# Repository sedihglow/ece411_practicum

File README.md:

# ece411_practicum
ece411 practicum project Team 16

# how to upload to ESP
1. Start upload from arduino IDE.
  - It will sit on connecting for this time.
2. Pull the reset pin low or unplug the device
3. Pull GPIO2 low with a button.
4. Let the reset pin go high or plug back in the device while gpio2 is low
  - The code should start uploading
5. let go of the GPIO2 button to ground.

# ESP setup program
1. Setup sensor pins
2. Setup I2C for moisture sensor
3. Try to connect to wifi using credentials in EEPROM
4. If credentials are bad, start a wifi hotspot on ESP
5. Connect to ESP using its wifi hotspot by connecting to the IP Address from a web browser
6. Once credentials are changed it reconnects using the new credentials.

# ESP main loop program flow
1. Check for user packet
2. if user sent a packet, handle the request for moisture threshold or pump time
3. read the moisture sensor
4. If the moisture sensor reads below threshold and water is in the tank, water plant
5. repeat 1-4

# user program
To compile use the makefile $make
To run you can use the makefile $make run
The user program will prompt the user with a menu
  - change moisture threshold
  - change pump time
  - exit program
  
The moisture threshold can be values of 1 to 1000

The pump time can be between 1 and 10 seconds

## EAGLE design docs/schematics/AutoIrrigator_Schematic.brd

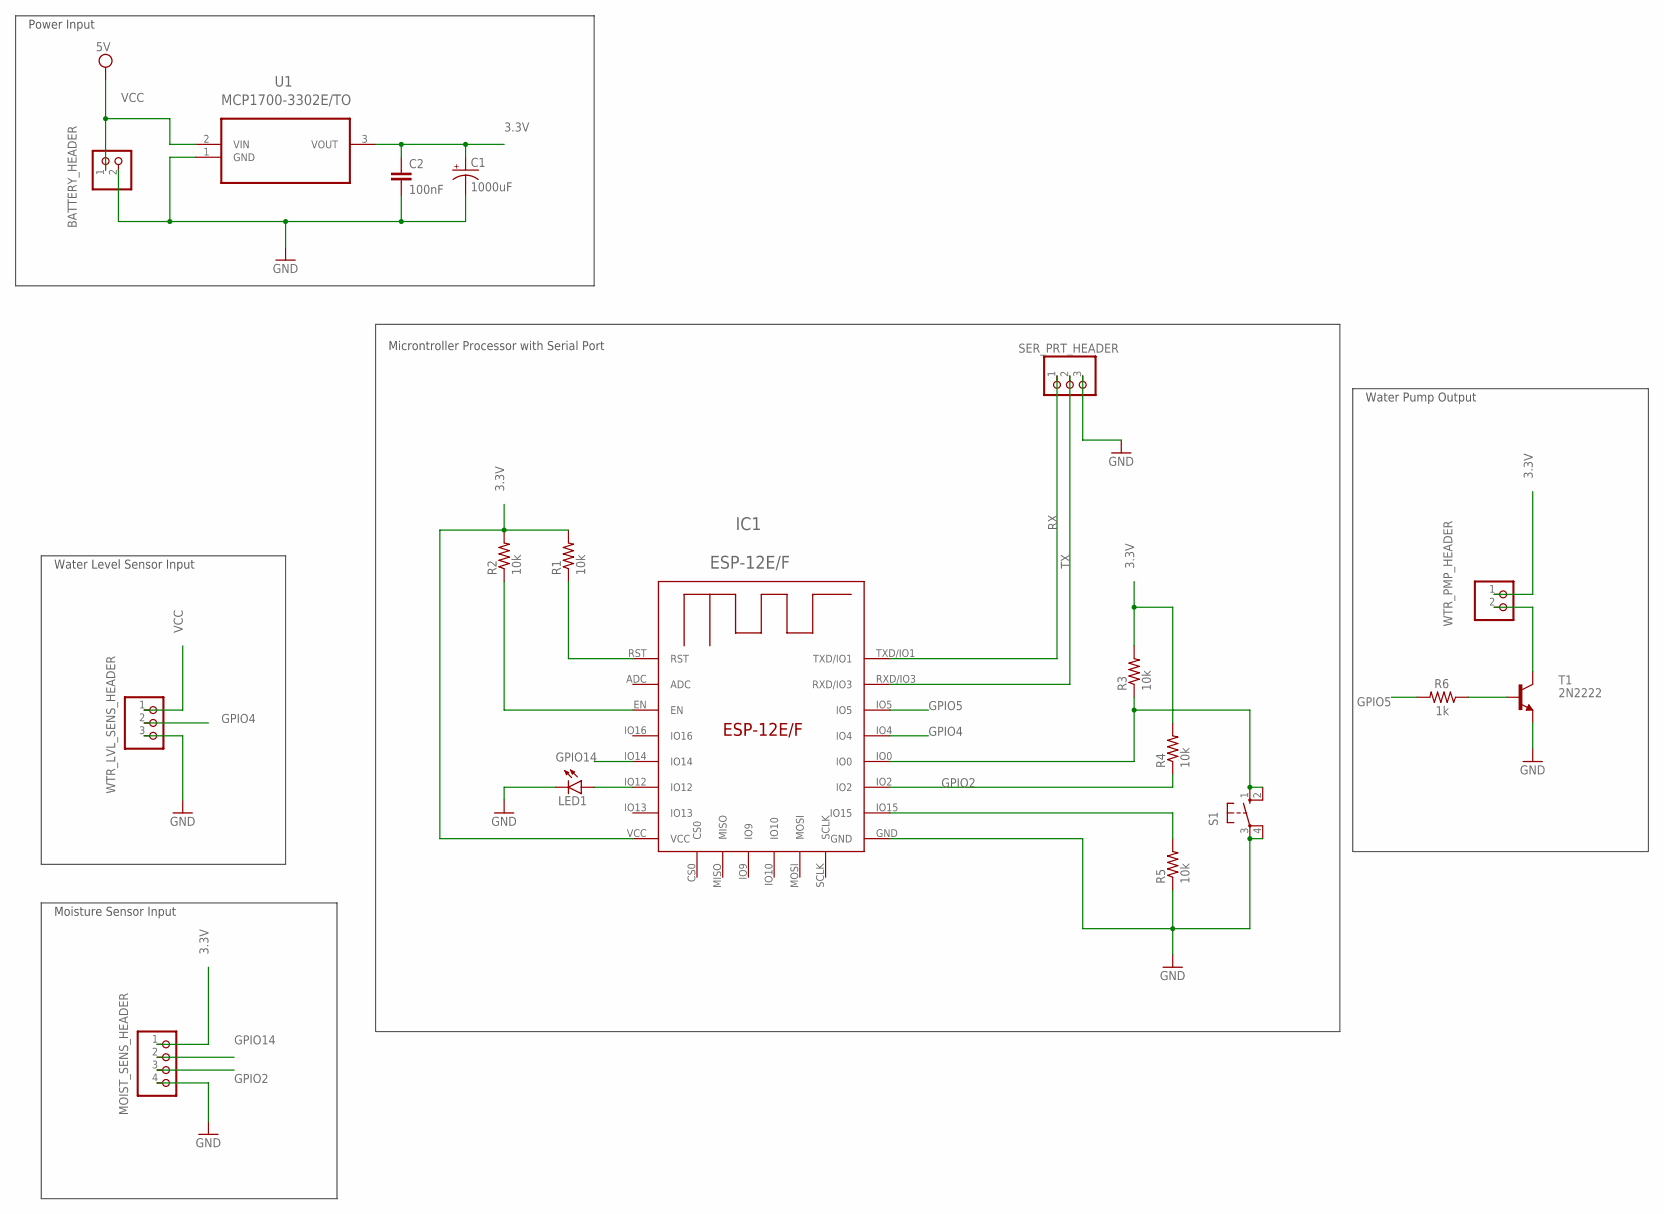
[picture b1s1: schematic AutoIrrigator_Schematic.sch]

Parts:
BATTERY_HEADER: PINHD-1X2; 1X02
C1: 1000uF; E2,5-6
C2: 100nF; C025-025X050
IC1: ESP-12E/F; ESP-12E
LED1: LED5MM
MOIST_SENS_HEADER: PINHD-1X4; 1X04
R1, R2, R3, R4, R5: 10k; 0204/7
R6: 1k; 0204/7
S1: 10-XX; B3F-10XX
SER_PRT_HEADER: SER_PRT_HEADER; 1X03
T1: 2N2222; TO18
U1: MCP1700-3302E/TO; TO127P254X495-3
WTR_LVL_SENS_HEADER: PINHD-1X3; 1X03
WTR_PMP_HEADER: PINHD-1X2; 1X02

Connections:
3.3V: C1.+, C2.1, IC1.VCC, MOIST_SENS_HEADER.1, R1.2, R2.2, R3.2, R4.2, U1.3 (VOUT), WTR_PMP_HEADER.1
COLLECTOR: T1.3 (C), WTR_PMP_HEADER.2
EMITTER: R6.1, T1.2 (B)
EN: IC1.EN, R2.1
GND: BATTERY_HEADER.2, C1.-, C2.2, IC1.GND, LED1.K (C), MOIST_SENS_HEADER.4, R5.1, S1.3, S1.4 (P1), SER_PRT_HEADER.3, T1.1 (E), U1.1 (GND), WTR_LVL_SENS_HEADER.3
GPIO0: IC1.IO0, R3.1, S1.1 (S), S1.2 (S1)
GPIO2: IC1.IO2, MOIST_SENS_HEADER.3, R4.1
GPIO4: IC1.IO4, WTR_LVL_SENS_HEADER.2
GPIO5: IC1.IO5, R6.2
GPIO12: IC1.IO12, LED1.A
GPIO14: IC1.IO14, MOIST_SENS_HEADER.2
GPIO15: IC1.IO15, R5.2
RST: IC1.RST, R1.1
RX: IC1.TXD/IO1, SER_PRT_HEADER.1
TX: IC1.RXD/IO3, SER_PRT_HEADER.2
VCC: BATTERY_HEADER.1, U1.2 (VIN), WTR_LVL_SENS_HEADER.1

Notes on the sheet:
Water Level Sensor Input
Power Input
Moisture Sensor Input
Microntroller Processor with Serial Port
Water Pump Output

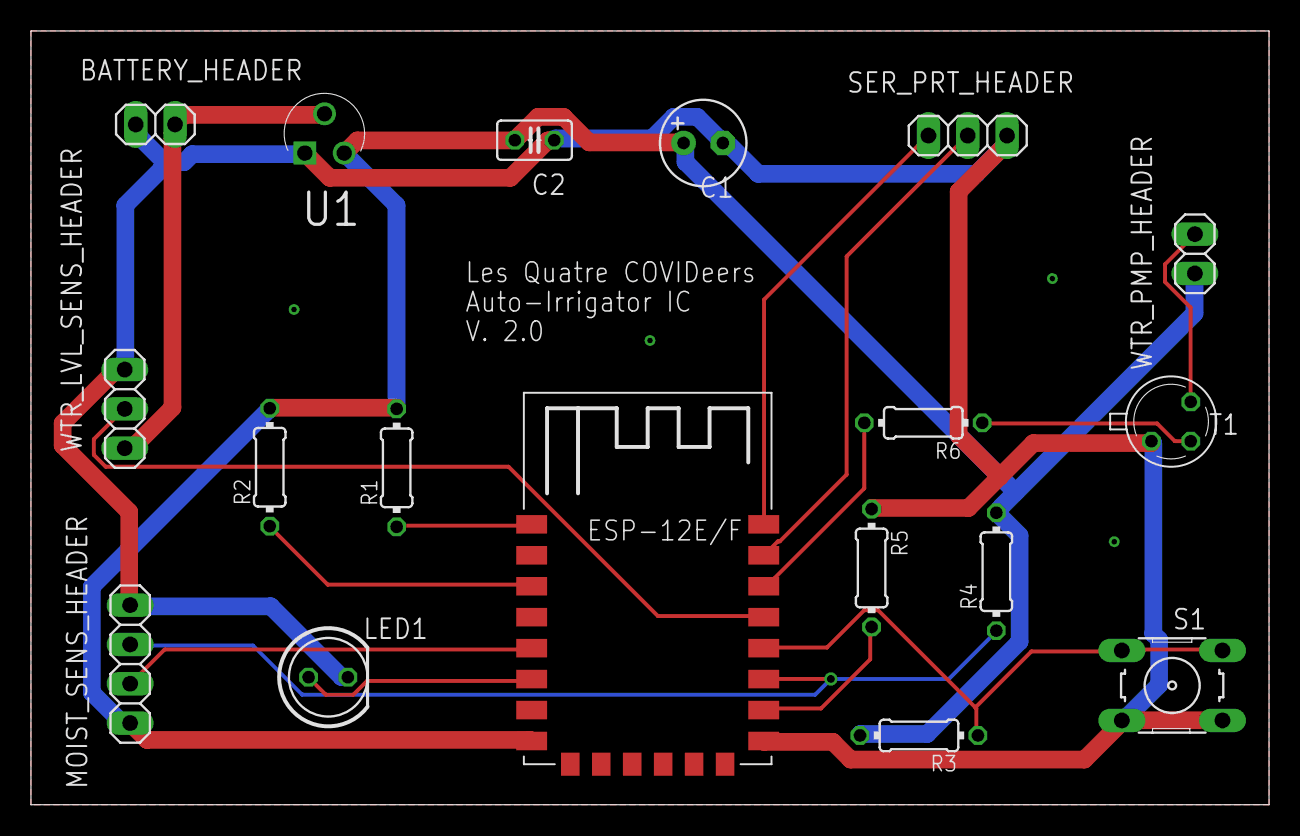
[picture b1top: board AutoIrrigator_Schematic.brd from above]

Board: 2 copper layers, 80.0 x 50.0 mm, 18 parts (0 on the bottom side), 16 nets.

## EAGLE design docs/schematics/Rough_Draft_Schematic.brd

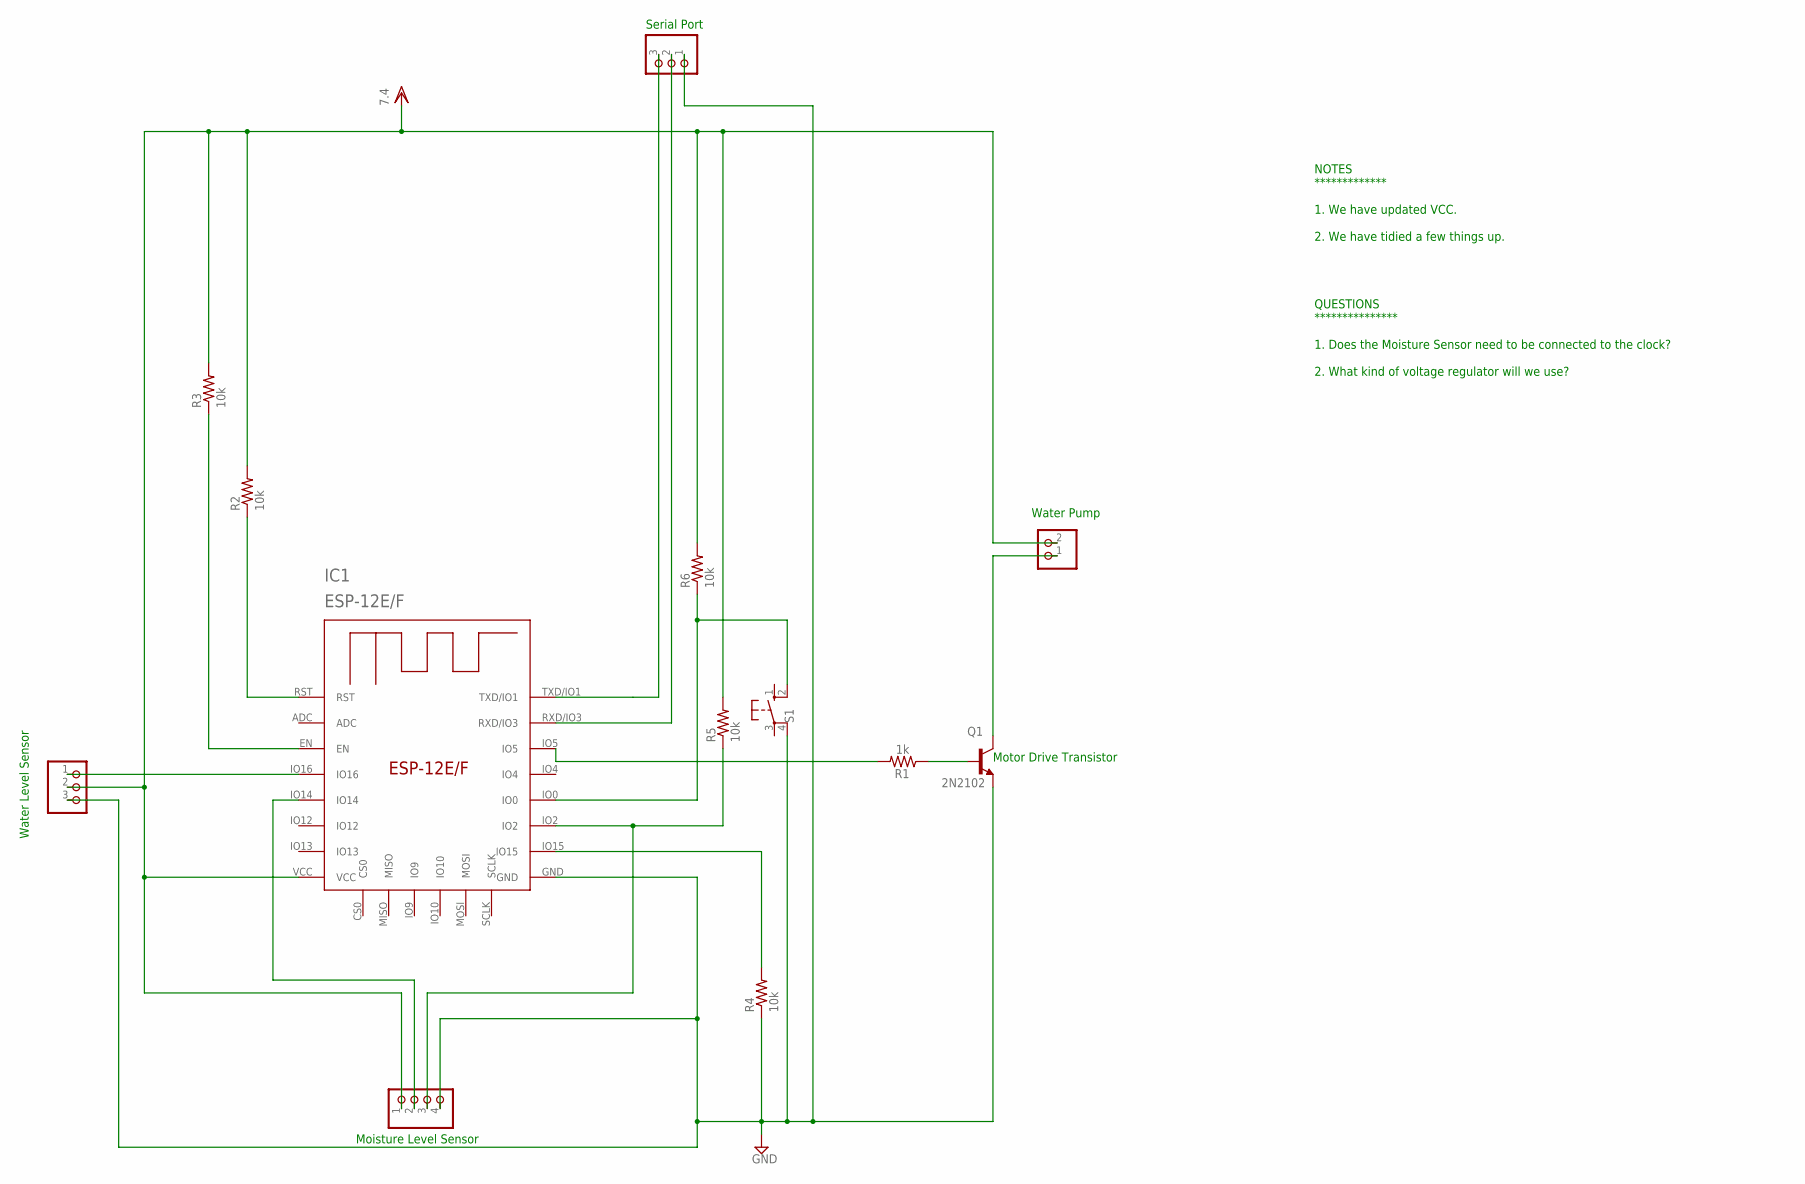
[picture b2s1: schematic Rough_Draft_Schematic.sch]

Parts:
IC1: ESP-12E/F; ESP-12E
JP1: PINHD-1X2; 1X02
JP3, JP4: PINHD-1X3; 1X03
JP5: PINHD-1X4; 1X04
Q1: 2N2102; TO5
R1: 1k; 0204V
R2, R3, R4, R5, R6: 10k; 0204V
S1: 10-XX; B3F-10XX

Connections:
GND: IC1.GND, JP3.3, JP4.1, JP5.4, Q1.1 (E), R4.1, S1.4 (P1)
MOISTURE_SENSOR: IC1.IO2, JP5.3, R5.1
unnamed: IC1.IO15, R4.2
unnamed: IC1.RXD/IO3, JP4.2
unnamed: IC1.EN, R3.1
unnamed: IC1.RST, R2.1
unnamed: IC1.IO0, R6.1, S1.2 (S1)
unnamed: IC1.IO14, JP5.2
unnamed: IC1.IO5, R1.2
unnamed: Q1.2 (B), R1.1
unnamed: JP1.1, Q1.3 (C)
VDD: IC1.VCC, JP1.2, JP3.2, JP5.1, R2.2, R3.2, R5.2, R6.2
WATER_LEVEL_SENSOR: IC1.IO16, JP3.1

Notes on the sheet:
Water Level Sensor
Moisture Level Sensor
Serial Port
Water Pump
Motor Drive Transistor
NOTES ************* 1. We have updated VCC. 2. We have tidied a few things up. QUESTIONS *************** 1. Does the Moisture Sensor need to be connected to the clock? 2. What kind of voltage regulator will we use?

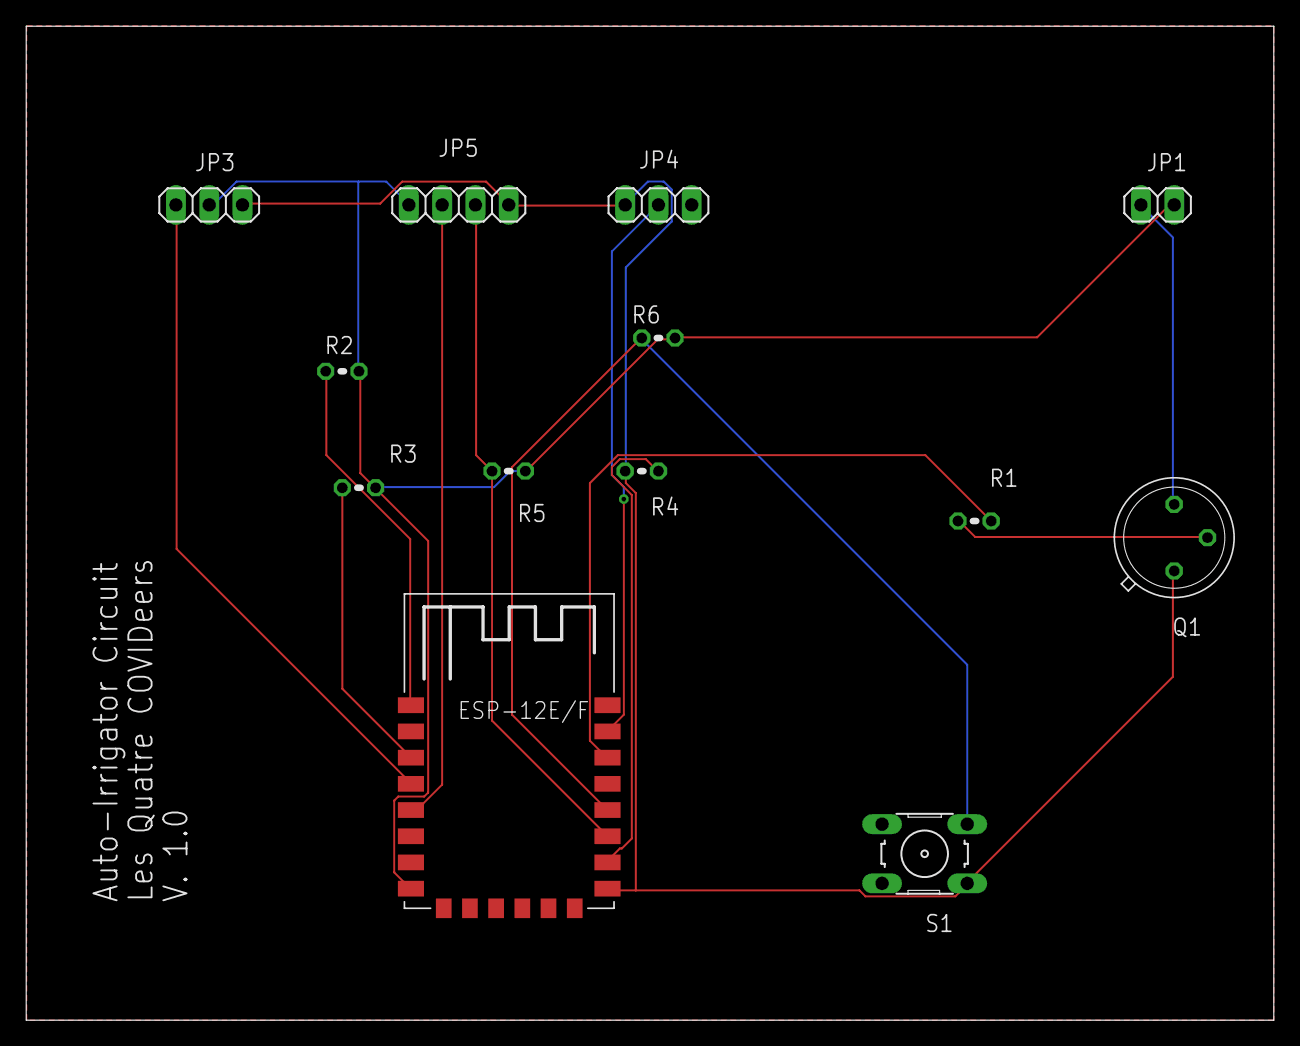
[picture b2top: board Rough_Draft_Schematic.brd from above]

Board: 2 copper layers, 95.2 x 75.9 mm, 13 parts (0 on the bottom side), 13 nets.

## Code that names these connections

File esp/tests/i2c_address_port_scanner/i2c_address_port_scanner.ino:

/* 
* i2c_port_address_scanner
* Scans ports D0 to D7 on an ESP8266 and searches for I2C device. based on the original code
* available on Arduino.cc and later improved by user Krodal and Nick Gammon (www.gammon.com.au/forum/?id=10896)
* D8 throws exceptions thus it has been left out
* written by jainrk
*/

#include <Wire.h>

void setup() {
  Serial.begin(115200);
  while (!Serial);             // Leonardo: wait for serial monitor
  Serial.println("\n\nI2C Scanner to scan for devices on each port pair D0 to D7");
  scanPorts();
}

uint8_t portArray[] = {16, 5, 4, 0, 2, 14, 12, 13};
//String portMap[] = {"D0", "D1", "D2", "D3", "D4", "D5", "D6", "D7"}; //for Wemos
String portMap[] = {"GPIO16", "GPIO5", "GPIO4", "GPIO0", "GPIO2", "GPIO14", "GPIO12", "GPIO13"};

void scanPorts() { 
  for (uint8_t i = 0; i < sizeof(portArray); i++) {
    for (uint8_t j = 0; j < sizeof(portArray); j++) {
      if (i != j){
        Serial.print("Scanning (SDA : SCL) - " + portMap[i] + " : " + portMap[j] + " - ");
        Wire.begin(portArray[i], portArray[j]);
        check_if_exist_I2C();
      }
    }
  }
}

void check_if_exist_I2C() {
  byte error, address;
  int nDevices;
  nDevices = 0;
  for (address = 1; address < 127; address++ )  {
    // The i2c_scanner uses the return value of
    // the Write.endTransmisstion to see if
    // a device did acknowledge to the address.
    Wire.beginTransmission(address);
    error = Wire.endTransmission();

    if (error == 0){
      Serial.print("I2C device found at address 0x");
      if (address < 16)
        Serial.print("0");
      Serial.print(address, HEX);
      Serial.println("  !");

      nDevices++;
    } else if (error == 4) {
      Serial.print("Unknow error at address 0x");
      if (address < 16)
        Serial.print("0");
      Serial.println(address, HEX);
    }
  } //for loop
  if (nDevices == 0)
    Serial.println("No I2C devices found");
  else
    Serial.println("**********************************\n");
  //delay(1000);           // wait 1 seconds for next scan, did not find it necessary
}

void loop() {
}

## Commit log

2020-10-15 saving homework 2
2020-10-23 Create Equipment
2020-10-23 moving equiptment to docs folder
2020-10-25 adding test file
2020-10-26 adding project proposal
2020-10-26 added block diagrams folder for images
2020-11-26 put appropriate files in docs, wrote inital tests for leds, water pump, water level sensor.
2020-11-26 added i2c address port scanner for finding i2c address on the bus
2020-11-26 moisure sensor test
2020-11-27 moisture sensor working and reading, water level sensor working and reading.
2020-11-27 fixed a couple compile bugs i didnt notice earlier
2020-11-27 currently working code, wls, pump, moisture sensor all programed.
2020-12-03 Can now change wifi credentials via a web browser and esp ip address on esp hotspot network. Worked a way to initialize the eeprom with initialization data, not overwriting it if eeprom is allready i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
2020-12-06 added test for udp packet reveive and send
2020-12-06 added a printout of esp IP address once connected to wifi
2020-12-06 setting up user source files and makefile
2020-12-06 added error printing functions and number conversion functions, need to clean up utility_sys with unneeded macros
2020-12-07 successfully sent packet from user to esp test code.
2020-12-07 added display functions and user input function
2020-12-07 user program sending messages to esp for changing moisture threshold and pump time. ESP stores the new value into the EEPROM and data struct
2020-12-08 tested and working.
2020-12-08 Update README.md
    Updated the readme
2020-12-08 Update README.md
    readme
2020-12-08 Update README.md
    updated readme
